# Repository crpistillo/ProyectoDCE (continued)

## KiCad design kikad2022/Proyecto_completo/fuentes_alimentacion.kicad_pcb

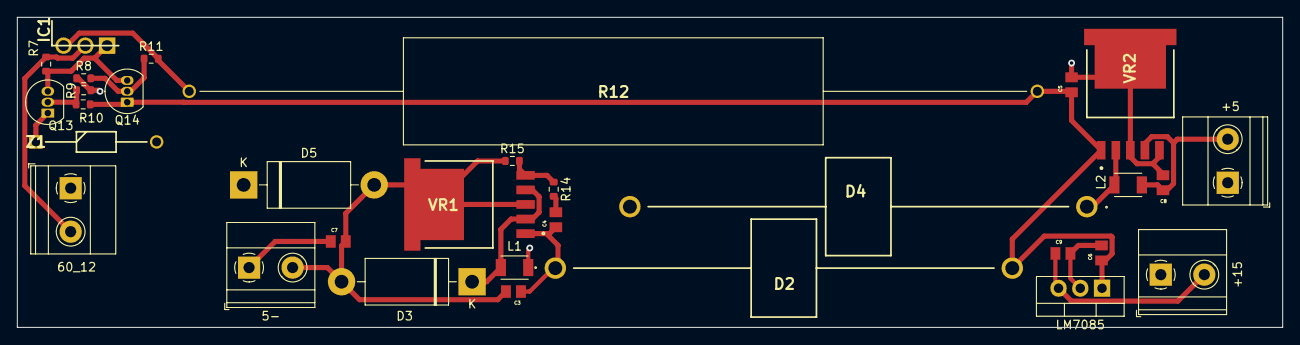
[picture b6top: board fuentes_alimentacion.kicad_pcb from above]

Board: 2 copper layers, 147.7 x 36.2 mm, 32 parts (0 on the bottom side), 16 nets.

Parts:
5-: 5-; TerminalBlock_Phoenix_MKDS-1,5-2-5.08_1x02_P5.08mm_Horizont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
60_12: 60_12; TerminalBlock_Phoenix_MKDS-1,5-2-5.08_1x02_P5.08mm_Horizont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
+5: 5+; TerminalBlock_Phoenix_MKDS-1,5-2-5.08_1x02_P5.08mm_Horizont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
+15: 15+; TerminalBlock_Phoenix_MKDS-1,5-2-5.08_1x02_P5.08mm_Horizont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
C3: 470u; CAPC2012X100N
C4, C9: 0.1u; CAPC2012X100N
C5: 680u; CAPC2012X100N
C6: 0.33u; CAPC2012X100N
C7, C8: 220u; CAPC2012X100N
D2: 1N5825; 1N5824
D3: 1N5820; D_DO-201AD_P15.24mm_Horizontal
D4: 1N5824
D5: 1N5400; D_DO-201AD_P15.24mm_Horizontal
IC1: BD681; TO254P290X760X1320-3P
L1, L2: 33u; L_TDK_NLV32_3.2x2.5mm
LM7085: LM7805_TO220; TO-220-3_Vertical
Q13, Q14: 2N3904; TO-92_Inline
R7, R8, R11: 2k; R_0603_1608Metric
R9: 5k; R_0603_1608Metric
R10: 27k; R_0603_1608Metric
R12: TUW15J47RE; TUW15J27RE
R14, R15: 47k; R_0603_1608Metric
VR1, VR2: LM2596S-5.0; KTT0005B
Z1: 1N4735A; DIOAD1413W86L463D238

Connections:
/reguladores/V+5: +5.2, C8.1, L2.2, VR2.4
/reguladores/V_+15: +15.2, C9.1, LM7085.3
/reguladores/V_-5: 5-.2, C3.2, C7.2, D3.2, D5.2, R15.1, VR1.3, VR1.6
/reguladores/V_IN_12-60V: 60_12.2, IC1.2, R7.1
GND: 5-.1, 60_12.1, +5.1, +15.1, C5.2, C6.2, C7.1, C8.2, C9.2, D4.2, D5.1, L1.2, LM7085.2, R8.1, R9.2, VR2.3, VR2.5, VR2.6, Z1.2
unnamed: C3.1, C4.1, D2.1, VR1.1
unnamed: C4.2, R14.2
unnamed: C5.1, C6.1, D2.2, LM7085.1, Q14.1, R10.1, R12.2, VR2.1
unnamed: D3.1, L1.1, VR1.2, VR1.4
unnamed: D4.1, L2.1, VR2.2
unnamed: IC1.1, Q13.3, Q14.3, R7.2
unnamed: IC1.3, R11.2, R12.1
unnamed: Q13.1, Z1.1
unnamed: Q13.2, R9.1, R10.2
unnamed: Q14.2, R8.2, R11.1
unnamed: R14.1, R15.2, VR1.5

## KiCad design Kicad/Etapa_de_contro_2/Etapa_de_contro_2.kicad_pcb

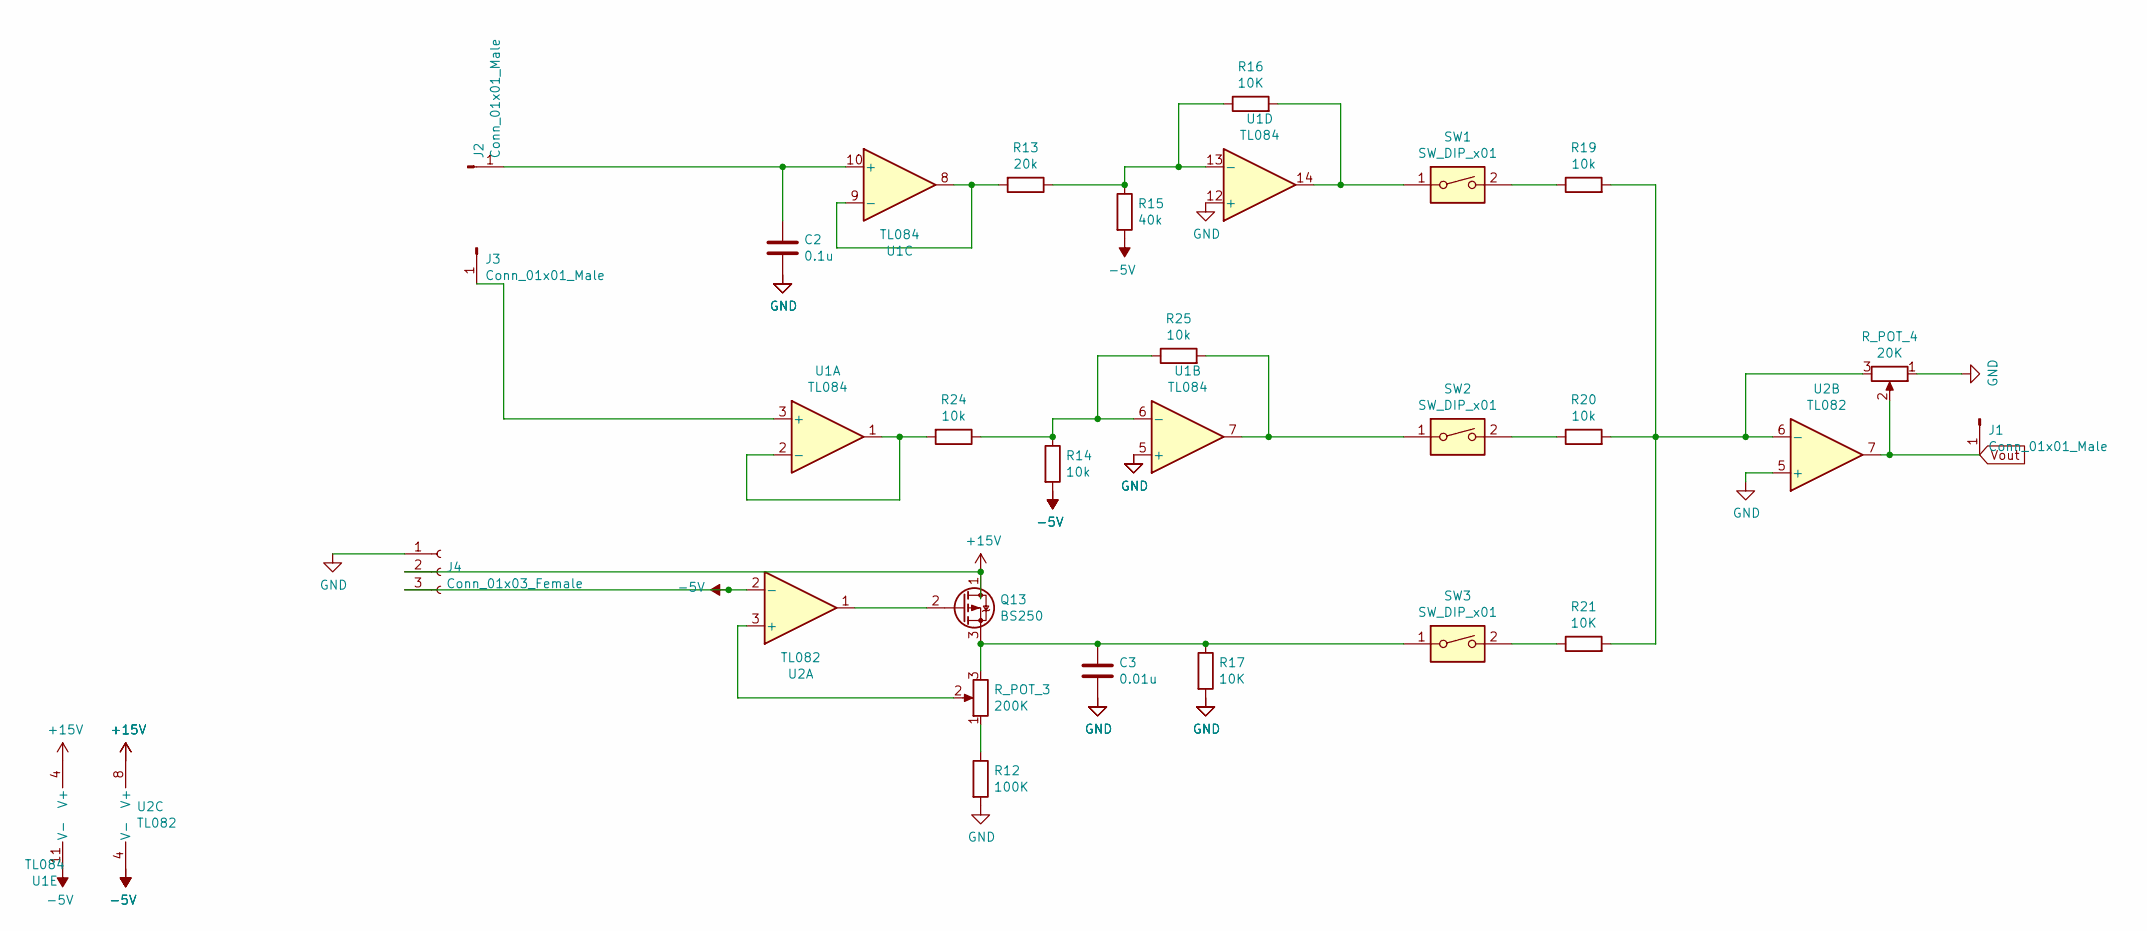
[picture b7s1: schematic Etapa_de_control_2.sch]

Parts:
C2: 0.1u; C_Disc_D3.8mm_W2.6mm_P2.50mm
C3: 0.01u; C_Disc_D3.8mm_W2.6mm_P2.50mm
J1, J2, J3: Conn_01x01_Male; PinHeader_1x01_P1.00mm_Vertical
J4: Conn_01x03_Female; PinHeader_1x03_P1.00mm_Vertical
Q13: BS250; TO-92_Inline
R12: 100K; R_0603_1608Metric
R13: 20k; R_0603_1608Metric
R14, R19, R20, R24, R25: 10k; R_0603_1608Metric
R15: 40k; R_0603_1608Metric
R16, R17, R21: 10K; R_0603_1608Metric
R_POT_3: 200K; Potentiometer_Bourns_3296W_Vertical
R_POT_4: 20K; Potentiometer_Bourns_3296W_Vertical
SW1, SW2, SW3: SW_DIP_x01; SW_PUSH_6mm
U1: TL084; SOIC-14W_7.5x9mm_P1.27mm
U2: TL082; DIP-8_W7.62mm

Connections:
+15V: J4.2, Q13.1 (D), U1.4 (V+), U2.8 (V+)
-5V: J4.3, R14.2, R15.2, U1.11 (V-), U2.2 (-), U2.4 (V-)
GND: C2.2, C3.2, J4.1, R12.2, R17.2, R_POT_4.1, U1.5 (+), U1.12 (+), U2.5 (+)
unnamed: C2.1, J2.1, U1.10 (+)
unnamed: C3.1, Q13.3 (S), R17.1, R_POT_3.3, SW3.1
unnamed: J3.1, U1.3 (+)
unnamed: Q13.2 (G), U2.1
unnamed: R12.1, R_POT_3.1
unnamed: R13.1, R15.1, R16.1, U1.13 (-)
unnamed: R13.2, U1.8, U1.9 (-)
unnamed: R14.1, R24.1, R25.1, U1.6 (-)
unnamed: R16.2, SW1.1, U1.14
unnamed: R19.1, SW1.2
unnamed: R19.2, R20.2, R21.2, R_POT_4.3, U2.6 (-)
unnamed: R20.1, SW2.2
unnamed: R21.1, SW3.2
unnamed: R24.2, U1.1, U1.2 (-)
unnamed: R25.2, SW2.1, U1.7
unnamed: R_POT_3.2, U2.3 (+)
Vout: J1.1, R_POT_4.2, U2.7

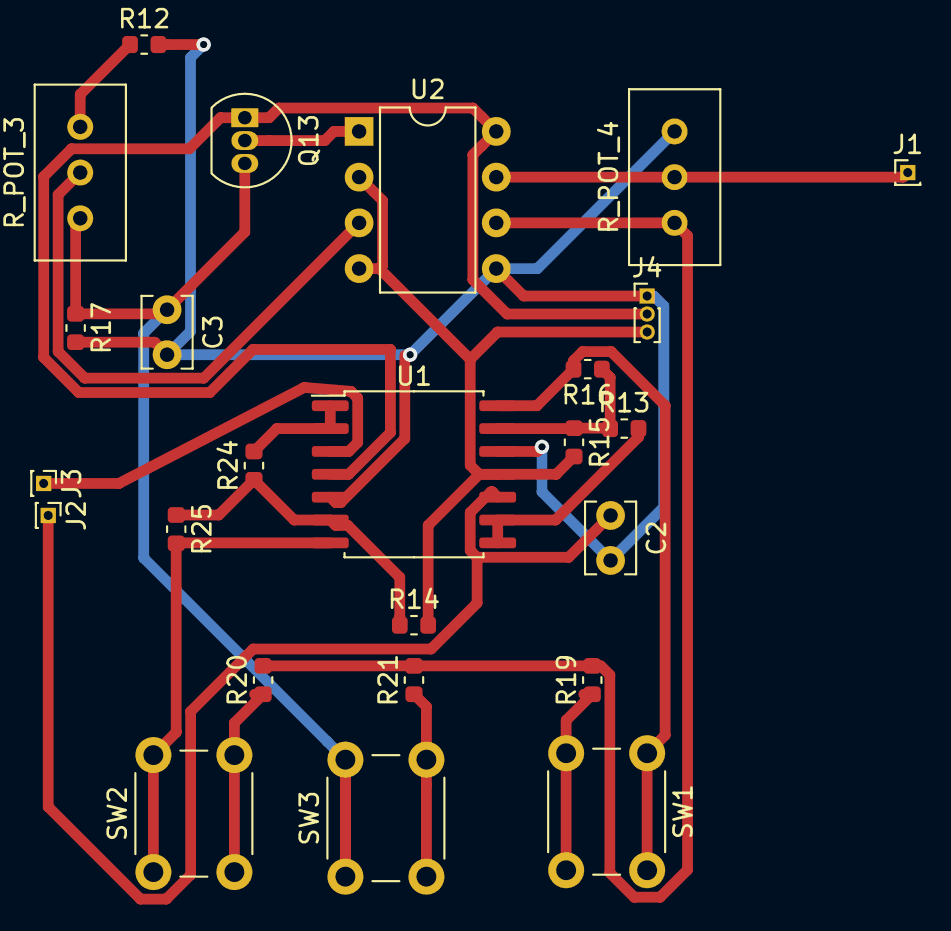
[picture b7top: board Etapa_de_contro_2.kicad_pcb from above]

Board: 2 copper layers, 25 parts (0 on the bottom side), 20 nets.

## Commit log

2020-04-14 Revert "Create Limitadores 20201.pdf"
    This reverts commit 02f4db08c5ebb4b2afe969496e4a434946a6c92a.
2020-04-14 Create hola123.txt
    Agregue el hola123 para dejar un saludo.
2020-04-16 Onda cuadrada y triangular
    ejemplos copiados del RASHID.
    la triangular no funciona
2020-04-16 Se acomodaron los ejemplos
2020-04-17 Onda cuadrada con LM555, presenta un pico
2020-04-17 Minor fixes
2020-04-17 Armo carpetas
2020-04-17 Elimine hola123
2020-04-20 Modelo y circuito con LM741
2020-04-20 Elimino carpeta duplicada
2020-04-20 Ejercicio 1
    A
2020-04-20 reemplace el EJERCICIO1
    a
2020-04-20 Grafico matlab
2020-04-20 Ejericicio 2
2020-04-20 sin querer
2020-04-20 grafico1a
2020-04-20 Cambie los ejes
2020-04-20 elimine2a
2020-04-20 Ejercicio 1b y 1c
2020-04-20 Punto 2a y b
2020-04-24 Ejercicio 3 (circ con limitador)
2020-04-24 Ej3 andando
2020-04-24 ESTA MAL
2020-04-24 Ejercicio unidos Mati
    Triangular cumple 15Vpp pero muy alta frecuencia
2020-04-24 7.5V pp en triangular
2020-04-24 Ejercicio 1 Vst=5
    Disparador schmitt centrado en 5 v
2020-04-24 Ej3, sacado del Sedra: != conexiones
2020-04-24 nada
2020-04-24 Ej Sedra == conexiones
2020-04-25 Carpeta y .asc f conmutada
2020-04-26 7.4V Pico
2020-04-29 Organizo carpetas
2020-04-29 gitignore
2020-05-01 elimine un txt
2020-05-01 elimine otro
2020-05-01 otro
2020-05-01 dfgdg
2020-05-01 Fixes
2020-05-01 Agrego carpeta Datasheets
    Con la del LM111
2020-05-01 Posible triangular
    vp=7.5 Freq=10k
2020-05-08 CircuitoLDO
2020-05-08 ahora si
2020-05-08 Ejercicio fuentes conmutadas
2020-05-09 ldo2
2020-05-10 Posible circuito tp1
2020-05-10 con sumador
2020-05-10 Regulador paralelo
2020-05-10 tl074
2020-05-11 Etapa1. Vean archivo Primera Etapa
2020-05-12 Actividad Realimentacion
2020-05-13 sque tildes y espacio
2020-05-14 Circuito
    Dudas: como centrar en cero la triangular ya que el capacitor no logra tener tensiones negativas.
2020-05-15 Definitivo
    De esos tres hay que sacar uno que tenga el duty y la frecuencia
2020-05-15 Con POTs para duty y frec
2020-05-20 Definitivo
    Circuit definitivo
2020-05-22 hola
2020-05-22 Saque un par de resistencias y la fuente de 6V
2020-05-23 Circuito definitivo
2020-05-23 Regulador
    Regulador con limitador de corriente
2020-05-23 Regulador20V
    Regulador con 20V a la salida y 60V a la entrada
2020-05-23 Salida de 15v
2020-05-23 Suma de señales cuadrada DC y triangular
2020-05-25 saque uno que no iba
2020-05-26 Cambio TL074 por TL084
2020-05-26 Agrego flip flop practico
2020-05-26 R emisores
2020-05-26 Correccion del sumador, R19,R20(baje la dc para que no sature el sumador) y R11(la salida de la cuadrada esta muy alta , la baje)
2020-05-27 frecuencias bajas arreglado
2020-05-27 graficos.m
2020-05-27 prolijo 3
2020-05-27 cuadrada centrada
2020-05-27 actualizo
2020-05-27 cuadrada ahora si centrada
    R14=14k
2020-05-27 Cambio nand por nor
2020-05-27 descomento sumador
2020-05-28 regulador
    regulador 60 a 30
2020-05-28 cambio mosfet por modelo
2020-05-28 DC ok
    Cambie Vcc-5 por V-5 lo mismo para la positiva.
    Tambien acomode la entrada al sumador( dejando las R=10k conectadas a este subcircuito.
    Por ultimo aclaro que la salida de la DC ahora queda en 0v si se cambia R19 y R20 que es el pot del offset se varia la continua
2020-05-28 flip-flop 15 V
2020-05-28 a bishman lo mataron
2020-05-29 Acoplo continua correcta a CIRCUITO_FINAL_PROLIJO
2020-05-29 actualizo flip-flop
2020-05-29 regulador final
2020-05-29 Regulador
    Regulador terminado y modelo del darlington
2020-05-29 Arreglo dependencia limitador
2020-05-29 carpeta
2020-05-29 al pan al vino vino
2020-05-29 Actualizacion final
2020-05-29 Informe al git
2020-06-03 algo del git
2020-06-04 Vss=-5V
2020-06-04 LM2575
2020-06-04 ffts
2020-06-04 asdfg
2020-06-05 regulador de menor tension y mayor rango de regulacion
2020-06-05 conmutado
2020-06-05 modelo 20954
2020-06-05 CLASE
2020-06-06 cambios en clase
2020-06-11 probando LM7815
2020-06-11 datasheet LM7815
2020-06-12 RegDePotencia es el regulador lineal con darlingotn de potencia
2020-06-12 Regulador Potencia (sin el Limitador)
    El LM7815 en la etapa de control tiene una corriente de entrada MUY grande
2020-06-13 kicad
2020-06-16 simulaciones actividad ampli clase B
2020-06-17 circuitos actividad5
2020-06-18 Kicad etapa de control
2020-06-18 KiCad reguladores
2020-06-25 rele
2020-06-26 Relay ideal, step up ideal
2020-06-26 half_bridge
2020-06-26 kicad_etapa_de_control_final
2020-06-29 autoguardad
2020-07-01 elimine
2020-07-01 reacomodacion
2020-07-03 full bridge
2020-07-03 Full Bridge ideal andando
2020-07-03 IRF3710
2020-07-07 half bridge con pequeno bug
2020-07-09 interfaz
2020-07-09 half bridge anda
2020-07-09 half bridge additions
2020-07-09 Valores hald bridge listos
2020-07-09 Halfbridge listo
2020-07-10 Kicad, etapa de control
2020-07-11 Correccion, GND
2020-07-13 kicad 1 sola placa, etapa de control
2020-07-14 agrego carpeta fullbridge
2020-07-16 Solucion problema del loop
2020-07-17 Idea de bertuccio
2020-07-18 Probando filtro LC en salida de halfbridge
2020-07-23 Kikad_potencia
2020-07-23 Actualizacion etapa potencia
    Joaco, ahi pude arreglar el problema era de las huellas que las habia descargado mal. acomode muy por arriba los componentes en el kicad ma;ana nos ponemos a ubicarlos el el lugar especifico
2020-07-23 LAZO CERRADO
2020-07-23 Actualizacion PCB
    Falta acomodar el GND y ver los Loops
2020-07-24 arreglo half
2020-07-24 carito anda a dormir
2020-07-28 asdfghjkl
2020-07-28 cambio en huellas del kikad
2020-07-30 Circuito prolijo
2020-07-30 Reacomodaciones en la carpeta de kicad, y se subio el PCB de la etapa de potencia
2020-07-30 modelos de footprints
2020-08-03 amplifica bien mati ke flashias ah
2020-08-03 fixe
2020-08-04 asdfghjk
2020-08-05 regulador
2020-08-08 Limitador Funcionando
    Circuito final con limitador
2020-08-10 Triangular_PWM_200K_4vp
2020-08-10 triangular andando
2020-08-12 driver arreglado
2020-08-13 agrego triangular
2020-08-14 Kicad Circuito de potencia FINAL
2020-08-25 PCB FINAL POTENCIA
2021-08-13 subo circuito que anda
2022-01-11 Actualizo circuito final: posible_circuito_potencia..
2022-01-21 update etapa control
2022-01-23 Update etapa de control y esquematicos del regulador
2022-01-23 update etapa de control a 500 Hz
2022-01-24 agrego step up andando pero dejo el ideal en el circuito completo
2022-01-24 agrego fuente conmutada de -5v LM2596-5
2022-01-24 regulador de tension LM2596
2022-01-24 conmutado modificado
2022-01-27 Agrego capacitores
    agrego capacitores a los reguladores LM7805 Y LM7815
2022-01-27 se agregan capacitores en los reguladores
2022-01-28 Circuito final potencia (prolijo), sin limitador
2022-01-29 Agrego fuente conmutada de 5V en el mismo circuito que la de -5V
2022-01-29 update circuito potencia y triangular
2022-02-05 Estabilizacion etapa potencia
2022-02-05 Update gitignore
2022-02-05 Update estabilizacion
2022-02-11 Kicad2022
2022-02-12 kikad_modificaciones
2022-02-13 Agrego reguladores conmutados, fuente lineal y cambio en etapa de control
2022-02-13 movi resistencia 10k
2022-02-13 Agrego recortador de limite superior de tension a la entrada
2022-02-13 Fuente Conmutada -2.5V
2022-02-14 update circuits
2022-02-14 update en resistencia
2022-02-15 Kikad_control+Potencia Definitivo
    Por favor que sea definitivo jajaj
